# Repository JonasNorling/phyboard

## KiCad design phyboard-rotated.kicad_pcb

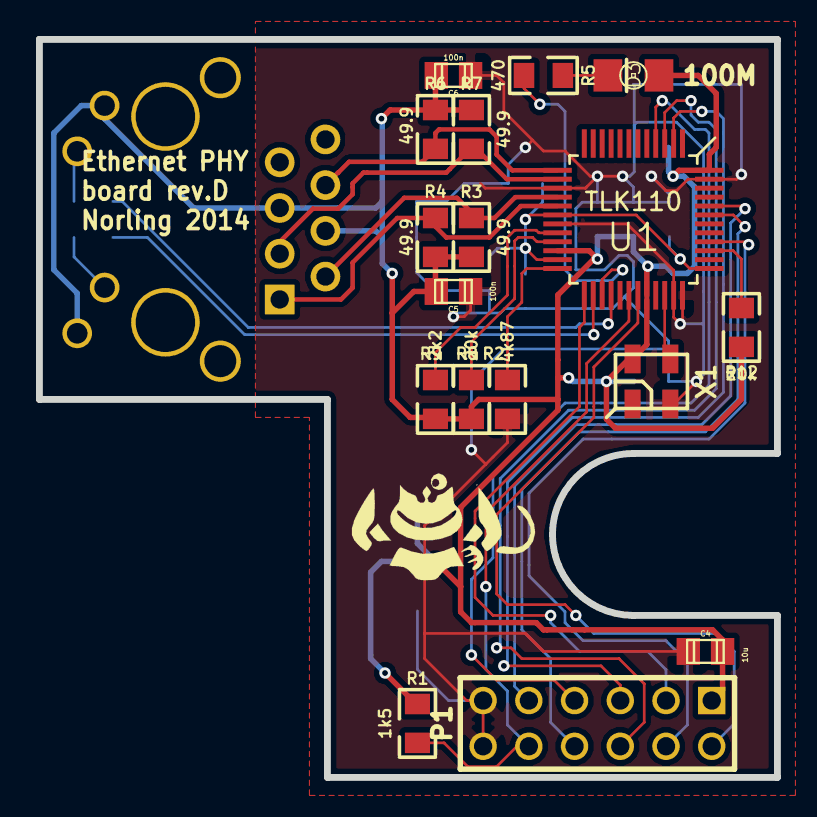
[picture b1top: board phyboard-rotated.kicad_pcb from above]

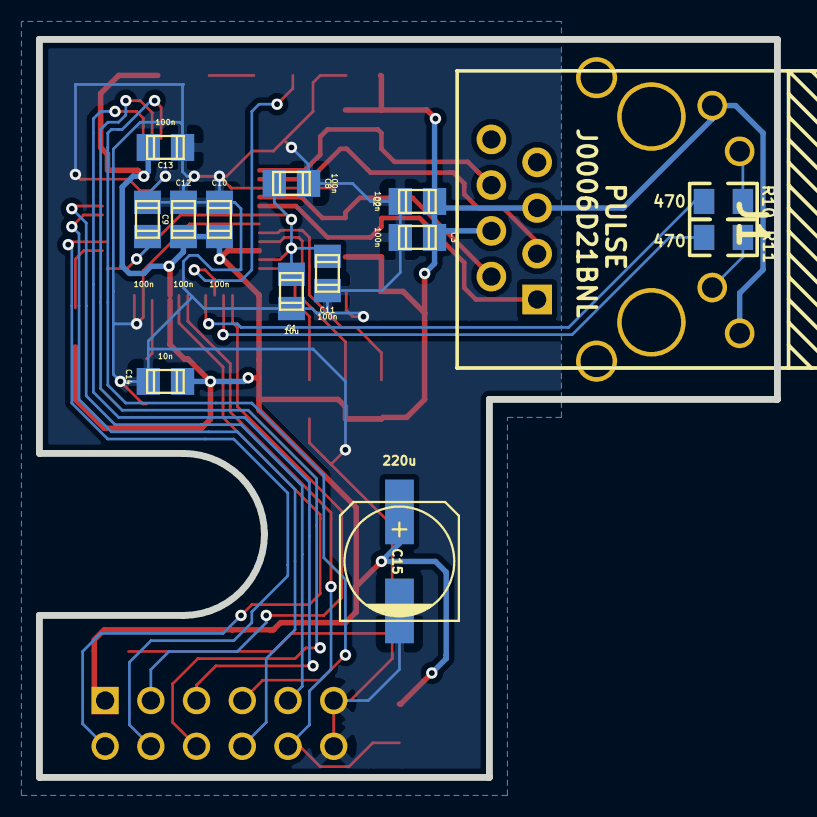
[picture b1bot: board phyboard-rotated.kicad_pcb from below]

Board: 2 copper layers, 41.0 x 41.0 mm, 31 parts (14 on the bottom side), 27 nets.

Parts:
C1, C4: 10u; c_0805
C2, C3, C5, C6, C8, C9, C10, C11, C12, C13: 100n; c_0805
C14: 10n; c_0805
C15: 220u; c_elec_6.3x5.3
D3: LED; LED-1206
J1: PULSE-J0006; pulse-J0006D21BNL
P1: CONN_6X2; pin_array_6x2
R1: 1k5; SM0805-jonas
R2: 4k87; SM0805-jonas
R3, R4, R6, R7: 49.9; SM0805-jonas
R5, R10, R11: 470; SM0805-jonas
R8, R12: 20k; SM0805-jonas
R9: 2k2; SM0805-jonas
U1: TLK110; QFP50P900X900-48M
X1: ASEMB-50.000MHZ-LC-T; oscillator-3.2x2.5

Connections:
+3.3V: C2.1, C3.1, C4.1, C5.1, C6.1, C10.1, C12.1, C13.1, C14.1, C15.1, D3.1, J1.4, J1.5, J1.9, J1.12, P1.1, R1.2, R3.1, R4.2, R6.1, R7.2, R8.2, R9.2, R12.2, U1.22, U1.32, U1.48, X1.4
/ETH_CLK: P1.3, U1.25
/ETH_CRS: P1.4, U1.40
/ETH_MDC: P1.2, U1.31
/ETH_MDIO: P1.10, R1.1, U1.30
/ETH_RxD0: P1.8, U1.43
/ETH_RxD1: P1.9, U1.44
/ETH_TX_EN: P1.5, U1.2
/ETH_TxD0: P1.6, U1.3
/ETH_TxD1: P1.7, U1.4
/LED1: J1.11, R10.2
/LED2: J1.10, R11.2
/LED3: D3.2, R5.2
/OSC: U1.34, X1.3
/PFB: C1.1, C8.1, C9.1, C11.1, U1.18, U1.23, U1.37
/RD+: J1.3, R7.1, U1.14
/RD-: J1.6, R6.2, U1.13
/RMII_MODE: R12.1, U1.39
/TD+: J1.1, R4.1, U1.17
/TD-: J1.2, R3.2, U1.16
GND: C1.2, C2.2, C3.2, C4.2, C5.2, C6.2, C8.2, C9.2, C10.2, C11.2, C12.2, C13.2, C14.2, C15.2, P1.11, P1.12, R2.2, U1.15, U1.19, U1.35, U1.36, U1.47, X1.2
unnamed: R2.1, U1.24
unnamed: R8.1, U1.21
unnamed: R9.1, U1.20
unnamed: R10.1, U1.28
unnamed: R5.1, U1.27
unnamed: R11.1, U1.26

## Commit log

2014-06-06 Import from SVN, r1313 "Rev C II".
2014-06-06 Add loose changes from working directory, rotated new board
2014-06-06 Using standard QFP50P900X900-48M for the PHY footprint
2014-06-06 Laying out rev D
2014-06-09 New rev.D with moved monkey
